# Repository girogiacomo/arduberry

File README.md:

# arduberry [WIP]
Rapberry Pi + Arduino

[ENG]

Disclaimer: part of the code present in this projest or libraries has been copied from other sources; libraries are property of HOPERF Micro-electronics Co., Ltd.

[ITA]

Limitazione di responsabilità: parte del codice presente in questo progetto è stato copiato da altre fonti; le librerie presenti sono di proprietà di HOPERF Micro-electronics Co., Ltd.

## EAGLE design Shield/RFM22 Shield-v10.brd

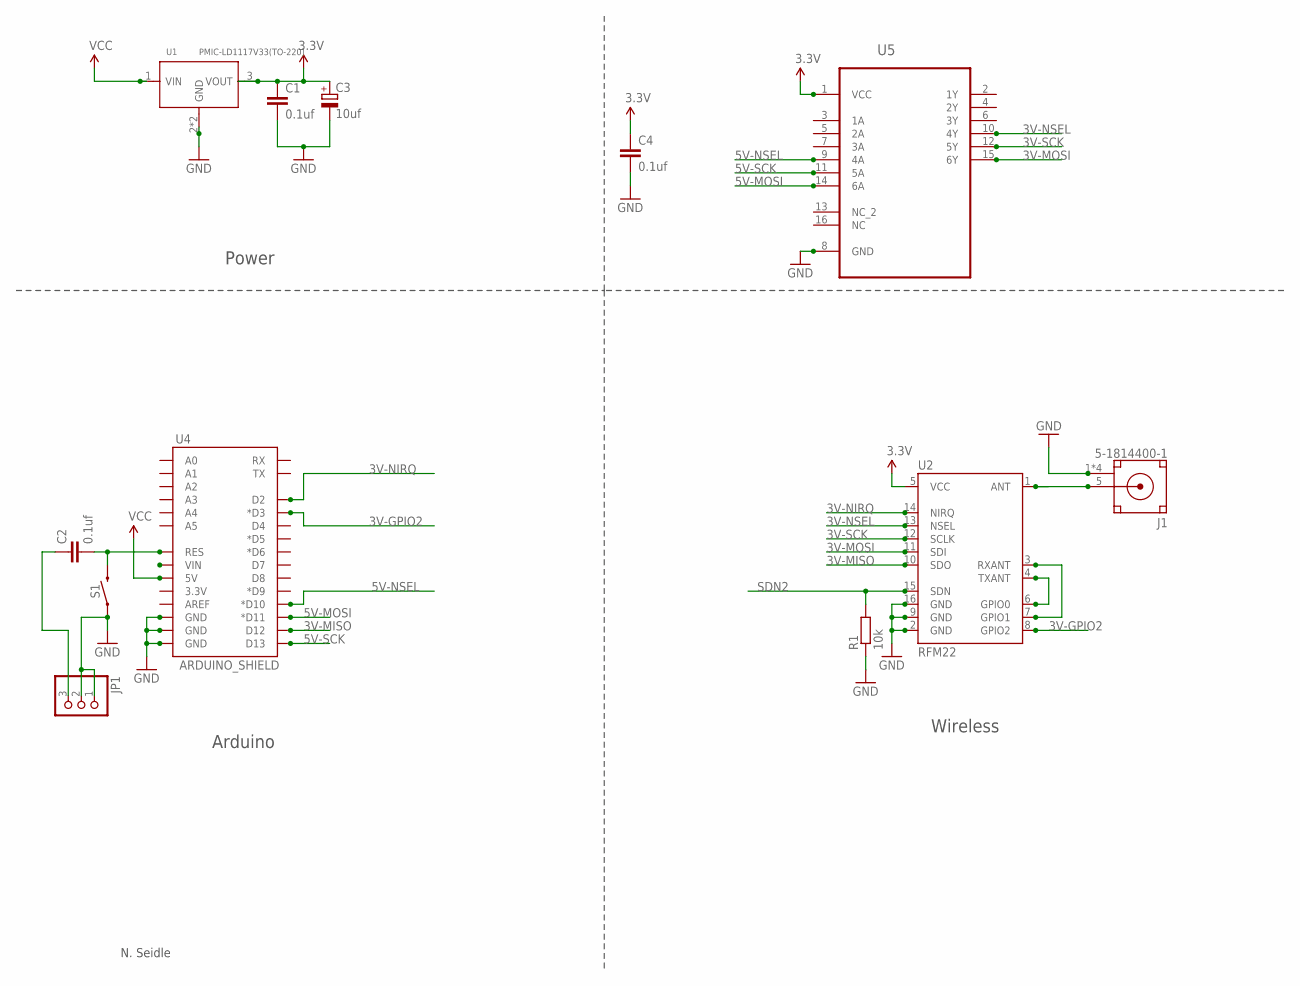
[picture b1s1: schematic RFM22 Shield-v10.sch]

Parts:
C1, C2, C4: 0.1uf; C050-030X075
C3: 10uf; E5-8,5
J1: 5-1814400-1; CONN_5-1814400-1
JP1: PINHD-1X3; 1X03
R1: 10k; 0207/10
S1: MOMENTARY-SWITCH-SPST-PTH-6.0MM; TACTILE_SWITCH_PTH_6.0MM
U1: PMIC-LD1117V33(TO-220); TO-220
U2: RFM22; RFM22-XXX-S2
U4: ARDUINO_SHIELD; DUEMILANOVE_SHIELD_NOHOLES
U5: 74HC4050N,652; DIP254P762X420-16

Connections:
3.3V: C1.1, C3.+, C4.1, U1.3 (VOUT), U2.5 (VCC), U5.1 (VCC)
3V-GPIO2: U2.8 (GPIO2), U4.D3 (*D3)
3V-MISO: U2.10 (SDO), U4.D12
3V-MOSI: U2.11 (SDI), U5.15 (6Y)
3V-NIRQ: U2.14 (NIRQ), U4.D2
3V-NSEL: U2.13 (NSEL), U5.10 (4Y)
3V-SCK: U2.12 (SCLK), U5.12 (5Y)
5V-MOSI: U4.D11 (*D11), U5.14 (6A)
5V-NSEL: U4.D10 (*D10), U5.9 (4A)
5V-SCK: U4.D13, U5.11 (5A)
ARST: C2.2, S1.3 (2), U4.RES
GND: C1.2, C3.-, C4.2, J1.1 (GND), J1.2 (GND), J1.3 (GND), J1.4 (GND), JP1.1, JP1.2, R1.1, S1.1, U1.2 (GND), U1.HEAT (GND), U2.2 (GND), U2.9 (GND), U2.16 (GND), U4.GND@0 (GND), U4.GND@1 (GND), U4.GND@2 (GND), U5.8 (GND)
unnamed: J1.5 (SIGNAL), U2.1 (ANT)
unnamed: U2.4 (TXANT), U2.6 (GPIO0)
unnamed: U2.3 (RXANT), U2.7 (GPIO1)
RES_HEAD: C2.1, JP1.3
SDN2: R1.2, U2.15 (SDN)
VCC: U1.1 (VIN), U4.5V

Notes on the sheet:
N. Seidle
Power
Arduino
Wireless

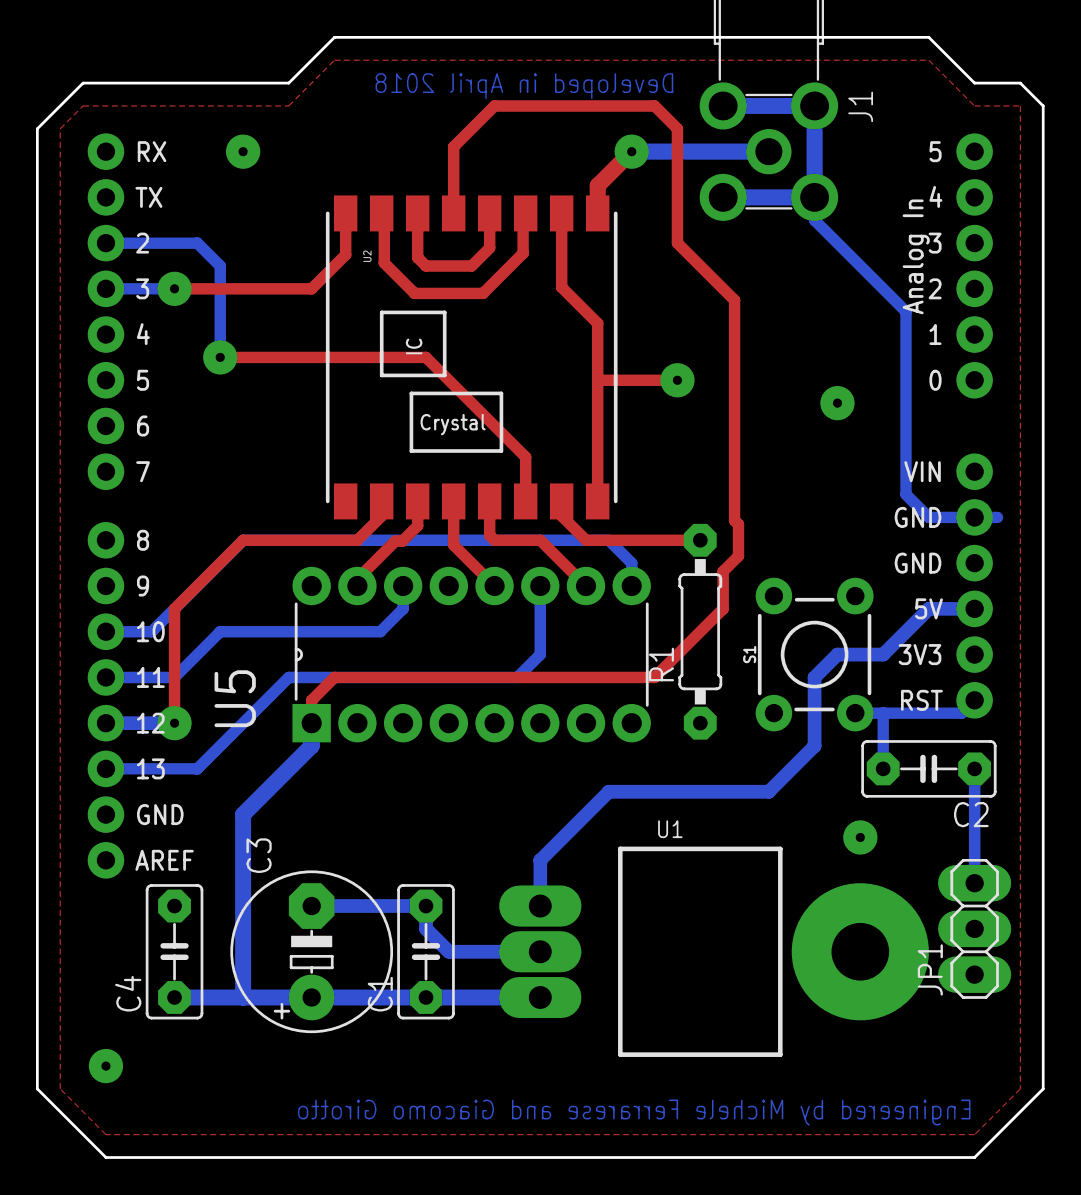
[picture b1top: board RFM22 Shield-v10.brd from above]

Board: 2 copper layers, 55.9 x 62.2 mm, 12 parts (0 on the bottom side), 18 nets.

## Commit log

2019-01-05 Wrong file... changed
2019-01-25 Android app bug fixes
2019-01-25 bug fix

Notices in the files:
parts and their libraries:
SparkFun-Switches: Licensing: Creative Commons ShareAlike 4.0 International - https://creativecommons.org/licenses/by-sa/4.0
